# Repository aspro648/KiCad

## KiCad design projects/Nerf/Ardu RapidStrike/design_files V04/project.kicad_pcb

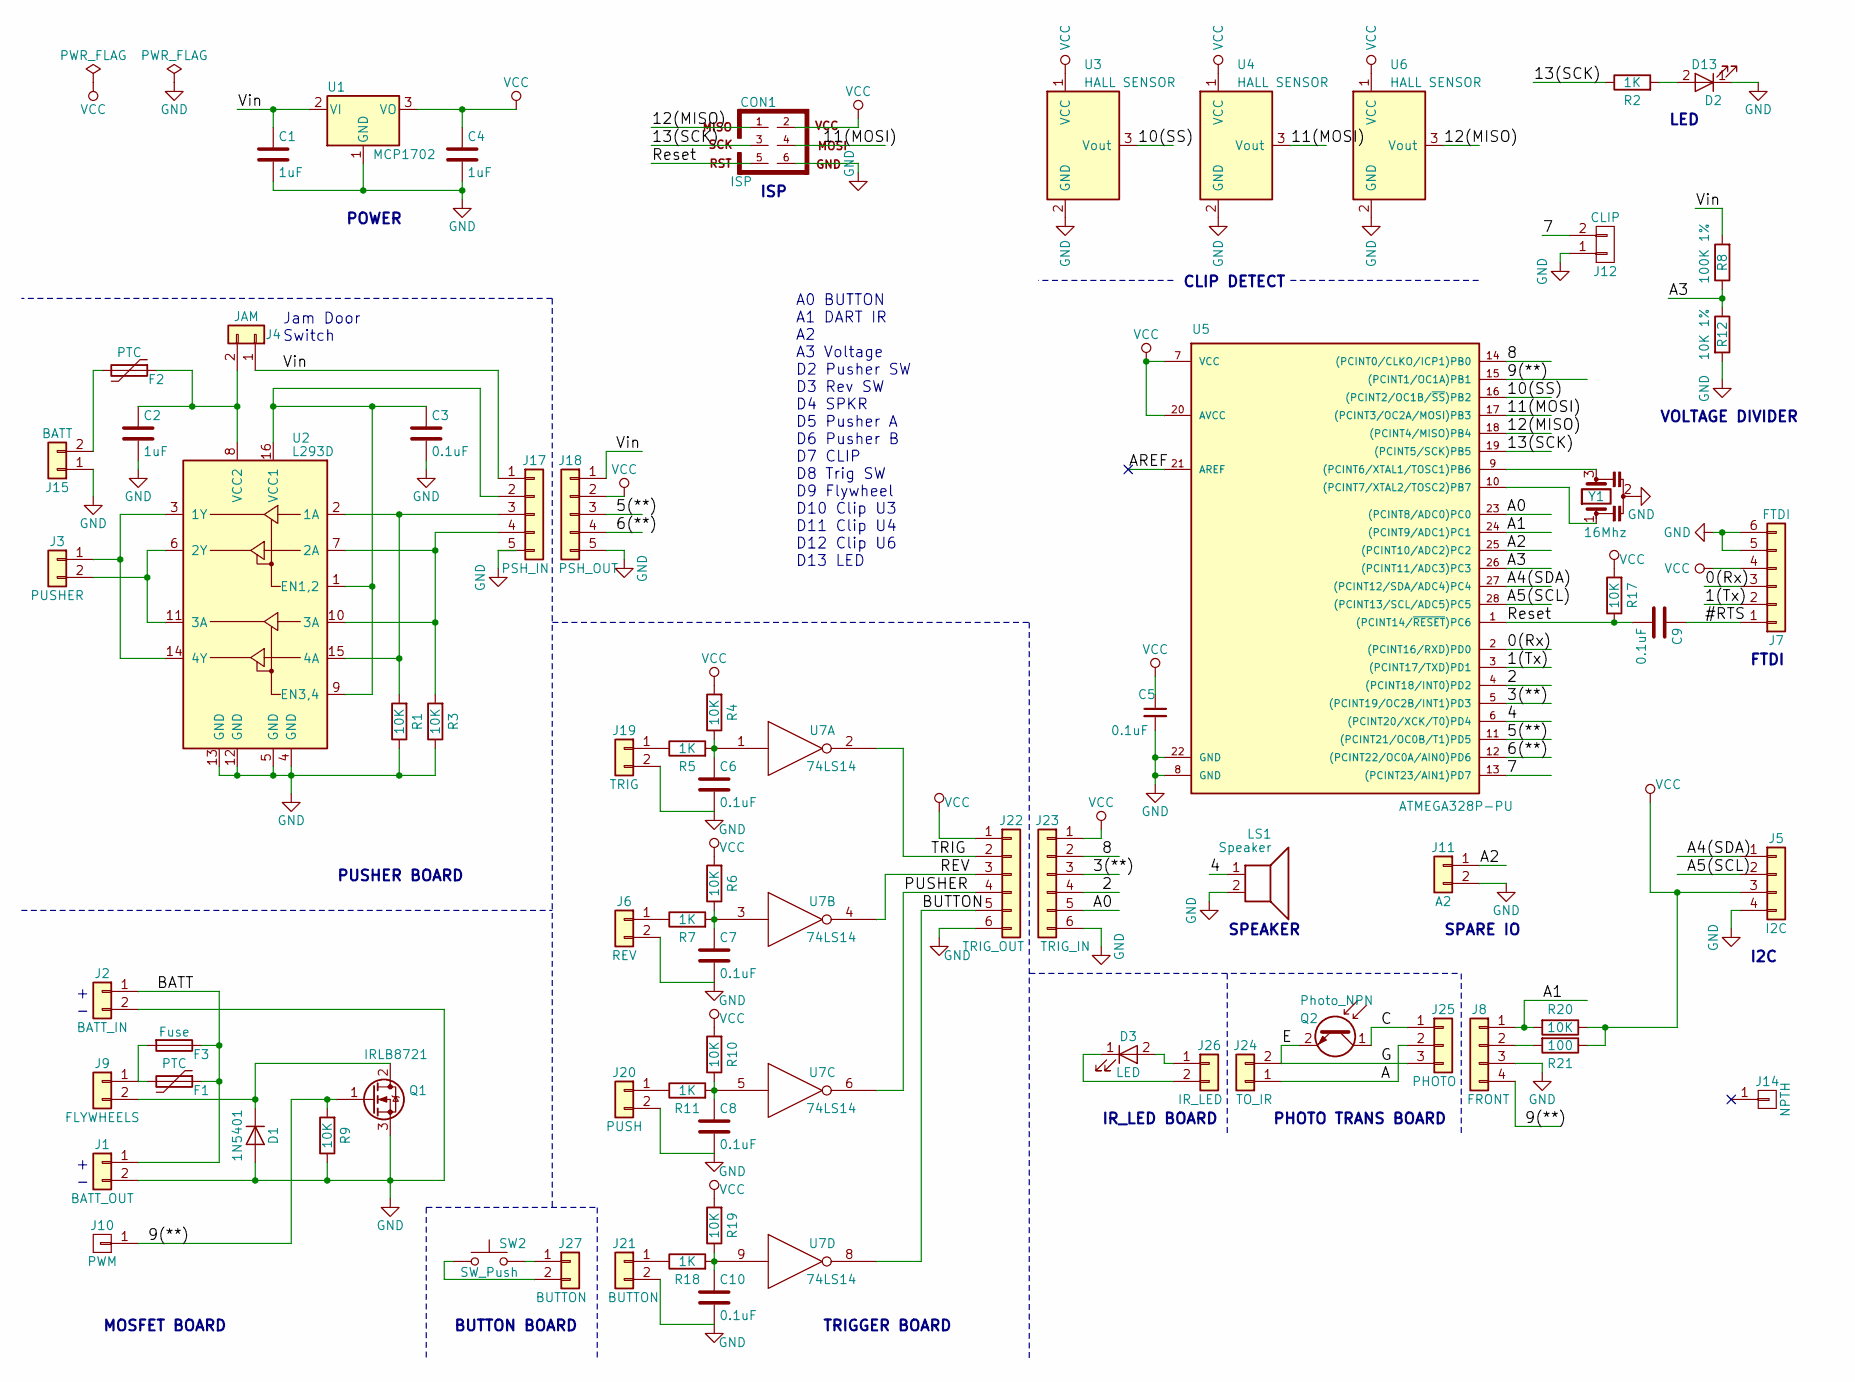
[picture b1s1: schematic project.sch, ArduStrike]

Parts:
C1, C2, C4: 1uF; C_Disc_D5.0mm_W2.5mm_P2.50mm
C3, C5, C6, C7, C8, C9, C10: 0.1uF; C_Disc_D3.4mm_W2.1mm_P2.50mm
CON1: ISP; Pin_Header_Straight_2x03_Pitch2.54mm
D1: 1N5401; D_DO-15_P12.70mm_Horizontal
D2: D13; LED_D3.0mm_Horizontal_O1.27mm_Z10.0mm
D3: LED; LED_D3.0mm
F1, F2: PTC; Fuse_Littelfuse-LVR125
F3: Fuse; BladeFuse-Mini_Keystone_3568
J1: BATT_OUT; TerminalBlock_Phoenix_PT-1,5-2-3.5-H_1x02_P3.50mm_Horizontal
J2: BATT_IN; TerminalBlock_Phoenix_PT-1,5-2-3.5-H_1x02_P3.50mm_Horizontal
J3: PUSHER; TerminalBlock_Phoenix_PT-1,5-2-3.5-H_1x02_P3.50mm_Horizontal
J4: JAM; TerminalBlock_Phoenix_PT-1,5-2-3.5-H_1x02_P3.50mm_Horizontal
J5: I2C; Molex_PicoBlade_53048-0410_04x1.25mm_Angled
J6: REV; Pin_Header_Straight_2x01_Pitch2.00mm
J7: FTDI; Pin_Header_Angled_1x06_Pitch2.54mm
J8: FRONT; Molex_PicoBlade_53048-0410_04x1.25mm_Angled
J9: FLYWHEELS; Flywheel_dual_terminals
J10: PWM; Pin_Header_Straight_1x01_Pitch2.00mm
J11: A2; Pin_Header_Straight_1x02_Pitch2.00mm
J12: CLIP; Molex_PicoBlade_53048-0210_02x1.25mm_Angled
J14: NPTH; SolderWirePad_single_2-5mmDrill
J15: BATT; TerminalBlock_Phoenix_PT-1,5-2-3.5-H_1x02_P3.50mm_Horizontal
J17: PSH_IN; Molex_PicoBlade_53047-0510_05x1.25mm_Straight
J18: PSH_OUT; Molex_PicoBlade_53048-0510_05x1.25mm_Angled
J19: TRIG; Pin_Header_Straight_2x01_Pitch2.00mm
J20: PUSH; Pin_Header_Straight_2x01_Pitch2.00mm
J21: BUTTON; Molex_PicoBlade_53047-0210_02x1.25mm_Straight
J22: TRIG_OUT; Molex_PicoBlade_53048-0610_06x1.25mm_Angled
J23: TRIG_IN; Molex_PicoBlade_53048-0610_06x1.25mm_Angled
J24: TO_IR; Pin_Header_Straight_1x02_Pitch2.00mm
J25: PHOTO; Pin_Header_Straight_1x03_Pitch2.00mm
J26: IR_LED; Pin_Header_Straight_1x02_Pitch2.00mm
J27: BUTTON; Pin_Header_Straight_1x02_Pitch2.00mm
LS1: Speaker; SPEAKER
Q1: IRLB8721; TO-220-3_Horizontal
Q2: Photo_NPN; LED_D3.0mm
R1, R3, R4, R6, R10, R17, R19, R20: 10K; R__P5.08mm
R2: 1K; R_Axial_DIN0204_L3.6mm_D1.6mm_P7.62mm_Horizontal
R5, R7, R11, R18: 1K; R__P5.08mm
R8: 100K 1%; R_Axial_DIN0204_L3.6mm_D1.6mm_P7.62mm_Horizontal
R9: 10K; R_Axial_DIN0204_L3.6mm_D1.6mm_P7.62mm_Horizontal
R12: 10K 1%; R_Axial_DIN0204_L3.6mm_D1.6mm_P7.62mm_Horizontal
R21: 100; R__P5.08mm
SW2: SW_Push; SW_PUSH_6mm
U1: MCP1702; TO-92_Inline_Narrow_Oval
U2: L293D; DIP-16_W7.62mm
U3, U4, U6: HALL SENSOR; Hall_Sensor
U5: ATMEGA328P-PU; DIP-28_W7.62mm
U7: 74LS14; DIP-14_W7.62mm
Y1: 16Mhz; Resonator-3pin_w7.0mm_h2.5mm

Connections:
/0(Rx): J7.3, U5.2 ((PCINT16/RXD)PD0)
/1(Tx): J7.2, U5.3 ((PCINT17/TXD)PD1)
/2: J23.4, U5.4 ((PCINT18/INT0)PD2)
/3(**): J23.3, U5.5 ((PCINT19/OC2B/INT1)PD3)
/4: LS1.1, U5.6 ((PCINT20/XCK/T0)PD4)
/5(**): J18.3, U5.11 ((PCINT21/OC0B/T1)PD5)
/6(**): J18.4, U5.12 ((PCINT22/OC0A/AIN0)PD6)
/7: J12.2, U5.13 ((PCINT23/AIN1)PD7)
/8: J23.2, U5.14 ((PCINT0/CLKO/ICP1)PB0)
/9(**): J8.4, J10.1, Q1.1 (G), R9.2, U5.15 ((PCINT1/OC1A)PB1)
/10(SS): U3.3 (Vout), U5.16 ((PCINT2/OC1B/~SS~)PB2)
/11(MOSI): CON1.4, U4.3 (Vout), U5.17 ((PCINT3/OC2A/MOSI)PB3)
/12(MISO): CON1.1, U5.18 ((PCINT4/MISO)PB4), U6.3 (Vout)
/13(SCK): CON1.3, R2.1, U5.19 ((PCINT5/SCK)PB5)
/#RTS: C9.1, J7.1
/A: J24.1, J25.2
/A0: J23.5, U5.23 ((PCINT8/ADC0)PC0)
/A1: J8.1, R20.2, U5.24 ((PCINT9/ADC1)PC1)
/A2: J11.1, U5.25 ((PCINT10/ADC2)PC2)
/A3: R8.1, R12.1, U5.26 ((PCINT11/ADC3)PC3)
/A4(SDA): J5.1, U5.27 ((PCINT12/SDA/ADC4)PC4)
/A5(SCL): J5.2, U5.28 ((PCINT13/SCL/ADC5)PC5)
/AREF: U5.21 (AREF)
/BATT: F1.1, F3.1, J1.1, J2.1
/BUTTON: J22.5, U7.8
/C: J25.1, Q2.1 (C)
/E: J24.2, J25.3, Q2.2 (E)
/PUSHER: J22.4, U7.6
/REV: J22.3, U7.4
/Reset: C9.2, CON1.5, R17.1, U5.1 ((PCINT14/~RESET~)PC6)
/TRIG: J22.2, U7.2
/Vin: C1.1, J4.1, J17.1, J18.1, R8.2, U1.2 (VI)
GND: C1.2, C2.2, C3.2, C4.2, C5.2, C6.2, C7.2, C8.2, C10.2, CON1.6, D1.2 (A), D2.1 (K), J1.2, J2.2, J5.4, J6.2, J7.5, J7.6, J8.3, J11.2, J12.1, J15.1, J17.5, J18.5, J19.2, J20.2, J21.2, J22.6, J23.6, LS1.2, Q1.3 (S), R1.1, R3.1, R9.1, R12.2, U1.1 (GND), U2.4 (GND), U2.5 (GND), U2.12 (GND), U2.13 (GND), U3.2 (GND), U4.2 (GND), U5.8 (GND), U5.22 (GND), U6.2 (GND), U7.7 (GND), Y1.2
unnamed: C2.1, F2.1, J4.2, U2.8 (VCC2)
unnamed: C3.1, J17.2, U2.1 (EN1,2), U2.9 (EN3,4), U2.16 (VCC1)
unnamed: C6.1, R4.1, R5.2, U7.1
unnamed: C7.1, R6.1, R7.2, U7.3
unnamed: C8.1, R10.1, R11.2, U7.5
unnamed: C10.1, R18.2, R19.1, U7.9
unnamed: D1.1 (K), J9.2, Q1.2 (D)
unnamed: D2.2 (A), R2.2
unnamed: D3.1 (K), J26.2
unnamed: D3.2 (A), J26.1
unnamed: F1.2, F3.2, J9.1
unnamed: F2.2, J15.2
unnamed: J3.1, U2.3 (1Y), U2.14 (4Y)
unnamed: J3.2, U2.6 (2Y), U2.11 (3A)
unnamed: J6.1, R7.1
unnamed: J8.2, R21.2
unnamed: J17.3, R1.2, U2.2 (1A), U2.15 (4A)
unnamed: J17.4, R3.2, U2.7 (2A), U2.10 (3A)
unnamed: J19.1, R5.1
unnamed: J20.1, R11.1
unnamed: J21.1, R18.1
unnamed: J27.1, SW2.2
unnamed: J27.2, SW2.1
unnamed: U5.9 ((PCINT6/XTAL1/TOSC1)PB6), Y1.3
unnamed: U5.10 ((PCINT7/XTAL2/TOSC2)PB7), Y1.1
VCC: C4.1, C5.1, CON1.2, J5.3, J7.4, J18.2, J22.1, J23.1, R4.2, R6.2, R10.2, R17.2, R19.2, R20.1, R21.1, U1.3 (VO), U3.1 (VCC), U4.1 (VCC), U5.7 (VCC), U5.20 (AVCC), U6.1 (VCC), U7.14 (VCC)

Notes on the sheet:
Jam Door Switch
VOLTAGE DIVIDER
CLIP DETECT
+ -
TRIGGER BOARD
MOSFET BOARD
PUSHER BOARD
BUTTON BOARD
PHOTO TRANS BOARD
IR_LED BOARD
A0 BUTTON A1 DART IR A2 A3 Voltage D2 Pusher SW D3 Rev SW D4 SPKR D5 Pusher A D6 Pusher B D7 CLIP D8 Trig SW D9 Flywheel D10 Clip U3 D11 Clip U4 D12 Clip U6 D13 LED
SPARE IO
FTDI
I2C
ISP
POWER
SPEAKER
LED

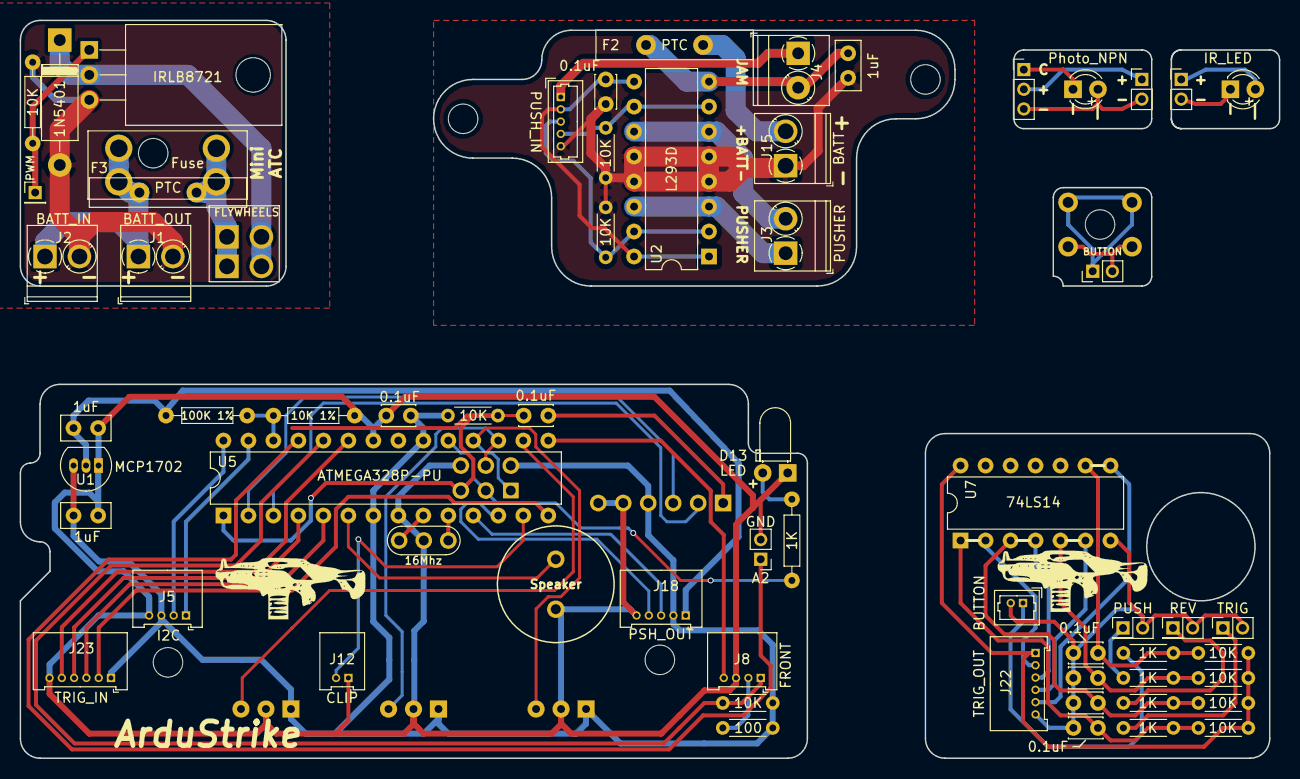
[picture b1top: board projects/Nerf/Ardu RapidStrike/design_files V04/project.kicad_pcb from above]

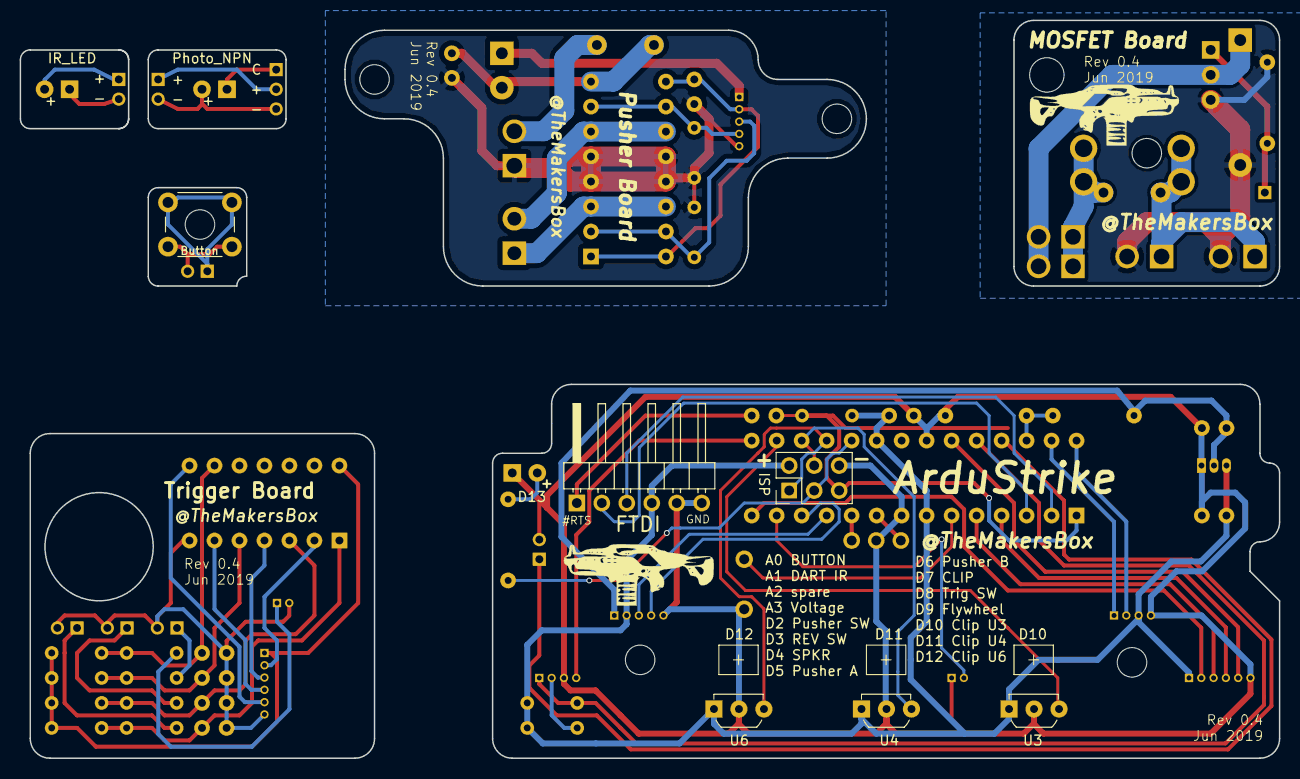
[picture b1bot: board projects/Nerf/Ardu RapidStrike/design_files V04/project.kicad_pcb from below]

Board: 2 copper layers, 128.0 x 75.0 mm, 76 parts (6 on the bottom side), 58 nets.

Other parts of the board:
J13: BUTTON; SolderWirePad_single_2-5mmDrill
J14#2, J14#3, J14#4, J14#5: NPTH; SolderWirePad_single_2-5mmDrill

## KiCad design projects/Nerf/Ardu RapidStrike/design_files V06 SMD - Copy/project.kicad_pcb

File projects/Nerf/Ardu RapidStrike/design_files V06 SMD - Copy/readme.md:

ArduStrike

MOSFET Board
-------------
- 1 ea., MOSFET N-CH 30V 62A TO-220AB, Infineon IRLB8721PBF, https://www.digikey.com/short/p4fhcm
- 1 ea., 1A Diode, S1KB
- 1 ea., 10K Resistors, 1/8W 5% generic, https://www.digikey.com/short/p4frj2 
- 1 ea., PTC RESET FUSE 16V 2.5A 2920SMD, https://www.digikey.com/short/p5cb11
- 3 ea., 2 POS 5.08mm terminal, https://www.digikey.com/short/p9tv29
- 1 ea., PTC Fuse 2.5A 1812, https://www.digikey.com/short/p5cbvf

Pusher Fuse 1206: 1A https://www.digikey.com/short/p532qq
Main: 1812: 3.5A https://www.digikey.com/short/p532pr

Pusher Board
-------------
- 1 ea., L293 H-Bridge, STMicroelectronics L293NE, https://www.digikey.com/short/pm20fd
- 2 ea., 10K Resistors, 1/8W 5% generic, https://www.digikey.com/short/p4frj2 
- 1 ea., CER 0.1UF 25V Y5V RADIAL 2.5mm lead spacing, generic, https://www.digikey.com/short/jn9pm2
- 1 ea., CER 1UF 25V X7R RADIAL 2.5 lead spacing, generic https://www.digikey.com/short/p4fr3w
- 1 ea., 5POS Picoblade header VERT, Molex 0530470510, https://www.digikey.com/short/pm2n8f
- 1 ea., PTC RESET FUSE 16V 2.5A RADIAL, https://www.digikey.com/short/pm20nc
- 2 ea., 2 POS 3.5mm terminal, https://www.digikey.com/short/p9tvn0
- 1 ea., 2 POS 5.08mm header, https://www.digikey.com/short/p9tv29

Trigger Board
--------------
- 1 ea., IC INVERTER SCHMITT 6CH 14DIP, TI SN74HC14N, https://www.digikey.com/short/pmzjfv
- 4 ea., CER 0.1UF 25V Y5V RADIAL 2.5mm lead spacing, generic, https://www.digikey.com/short/jn9pm2
- 4 ea., 1K Ohm Resistors, 1/8W 5% generic, https://www.digikey.com/short/p4fr81
- 4 ea., 10K Resistors, 1/8W 5% generic, https://www.digikey.com/short/p4frj2 
- 1 ea., 6POS PicoBlade header, https://www.digikey.com/short/p4wz22
- 1 ea., 2POS Picoblade header, https://www.digikey.com/short/p4wz0w

Main Board
----------------
- 1 ea., IC MCU 8BIT 32KB FLASH 32TQFP, https://www.digikey.com/short/p5cb88
- 1 ea., Y1 CER RES 16.0000MHZ 15PF SMD, CSTCE16M0V53-R0, https://www.digikey.com/short/j2b9cm
- 1 ea., IC REG LINEAR 5V 250MA SOT89-3, Microchip MCP1702-5002E/TO, https://www.digikey.com/short/p5cbrh
- 3 ea., Hall Effect Sensor, Diodes Incorporated AH9246-P-B, https://www.digikey.com/short/p5cb4f
- 1 ea., 0.96 Inch 128x64 I2C OLED, https://www.amazon.com/gp/product/B072Q2X2LL/
- 1 ea., Header 6 POS RA, 

- 2 ea., CER 0.1UF 25V Y5V RADIAL 2.5mm lead spacing, generic, https://www.digikey.com/short/jn9pm2
- 2 ea., CER 1UF 25V X7R RADIAL 2.5 lead spacing, generic https://www.digikey.com/short/p4fr3w

- 1 ea., 3mm LED red, https://www.digikey.com/short/pmwzdf
- 1 ea., 3mm IR LED, https://www.digikey.com/short/pmwzdq
- 1 ea., NPN photo transistor, https://www.digikey.com/short/pmwzdb

- 1 ea., 100 ohm resistor 1/8W 5% generic, https://www.digikey.com/short/pmwz22
- 1 ea., 1K ohm resistor 1/8W 5% generic, https://www.digikey.com/short/pmwzwq
- 2 ea., 10K Resistors, 1/8W 5% generic, https://www.digikey.com/short/p4frj2 

- 1 ea., 10K Resistors, 1/4W 1%, https://www.digikey.com/short/p4fr2q
- 1 ea., 100K Resistors, 1/4W 1%, https://www.digikey.com/short/p9tnc3

- 1 ea., SWITCH TACTILE SPST-NO 0.05A 24V, https://www.digikey.com/short/p4w42v
- 1 ea., Piezo speaker, TDK PS1240P02CT3,  https://www.digikey.com/short/pmwzfc

- 1 ea., 2POS Picoblade header, https://www.digikey.com/short/p4wz0w
- 1 ea., 2POS PicoBlade housing, https://www.digikey.com/short/p4wz0d

- 1 ea., 3POS Picoblade header, https://www.digikey.com/short/pmwzfb
- 1 ea., 3POS PicoBlade housing, https://www.digikey.com/short/pmwzf2

- 1 ea., 4POS Picoblade header, https://www.digikey.com/short/p4wz0m
- 2 ea., 4POS PicoBlade housing, https://www.digikey.com/short/p4wzd1

- 1 ea., 5POS Picoblade header, https://www.digikey.com/short/p4wzdp
- 2 ea., 5POS PicoBlade housing, https://www.digikey.com/short/p4wzdb

- 1 ea., 6POS PicoBlade header, https://www.digikey.com/short/p4wz22
- 2 ea., 6POS PicoBlade housing, https://www.digikey.com/short/p4wz28

12" PRE-CRIMP 1853 RED, https://www.digikey.com/short/p4wzvf
12" PRE-CRIMP 1853 BLACK, https://www.digikey.com/short/p4wz1p
12" PRE-CRIMP 1853 BLUE, https://www.digikey.com/short/p4wz14
12" PRE-CRIMP 1853 ORANGE, https://www.digikey.com/short/p4wz1r
12" PRE-CRIMP 1853 GREEN, https://www.digikey.com/short/p4w4c4

10" PRE-CRIMP 1852 RED, https://www.digikey.com/short/p937zh
10" PRE-CRIMP 1852 BLACK, https://www.digikey.com/short/p937zv
10" PRE-CRIMP 1852 YELLOW, https://www.digikey.com/short/p9374t
10" PRE-CRIMP 1852 GREEN, https://www.digikey.com/short/p9374z
10" PRE-CRIMP 1852 ORANGE, https://www.digikey.com/short/p9374f
10" PRE-CRIMP 1852 BLUE, https://www.digikey.com/short/p937mc

16 AWG Silicone wire, https://www.amazon.com/BNTECHGO-Silicone-Flexible-Strands-Stranded/dp/B00TG1TRL2
18 AWG Silicone wire (7.5A, $0.40/ft), https://www.amazon.com/Silicone-Electrical-Conductor-Parallel-Flexible/dp/B07FMRDP87
16 AWG Silicone wire (12A, $0.70/ft), https://www.amazon.com/Silicone-Electrical-Conductor-Parallel-Flexible/dp/B07FMLVF84

XT60 connector male

Optional:
FTDI SERIAL TTL-232 USB CABLE, https://www.digikey.com/short/p4w47d
SPARKFUN FT231X BREAKOUT, https://www.digikey.com/short/p4w4qb

Motor Spec Sheet:
----------------
https://docs.google.com/spreadsheets/d/12gOU-GbuqdGVzpOjZJvQ_gq1Nmw63c_sd13Wt4bfn1E/edit#gid=0

Revisions
----------------
0.1 Added push button to A0.
0.3 Removed XT30 connectors, added PTC, fuse holder.
0.4 Major component repositioning
0.5 Trigger moved clip connector
	Pusher Bat conn to 5.08mm.
	Mosfet layout change

License
----------------
[Attribution-ShareAlike 3.0 United States (CC BY-SA 3.0 US)](https://creativecommons.org/licenses/by-sa/3.0/us/)

You are free to:

- Share — copy and redistribute the material in any medium or format
- Adapt — remix, transform, and build upon the material

Under the following terms:

- Attribution — You must give appropriate credit, provide a link to the license, and indicate if changes were made. You may do so in any reasonable manner, but not in any way that suggests the licensor endorses you or your use.
- ShareAlike — If you remix, transform, or build upon the material, you must distribute your contributions under the same license as the original.

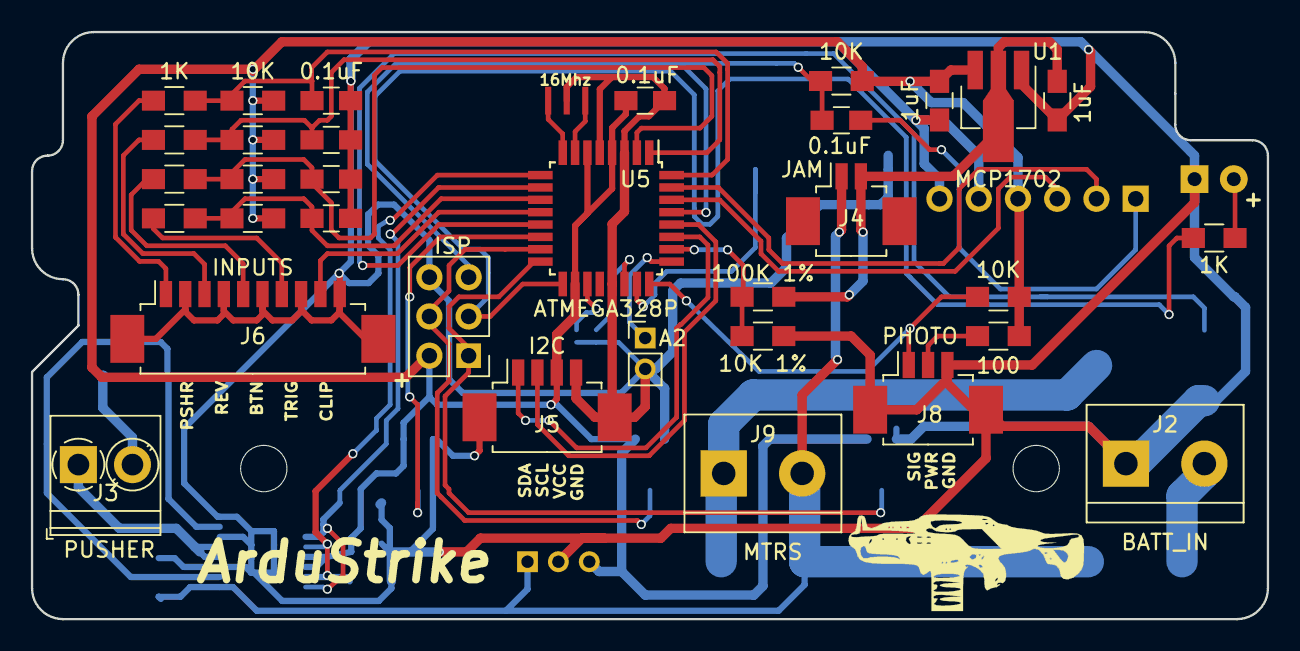
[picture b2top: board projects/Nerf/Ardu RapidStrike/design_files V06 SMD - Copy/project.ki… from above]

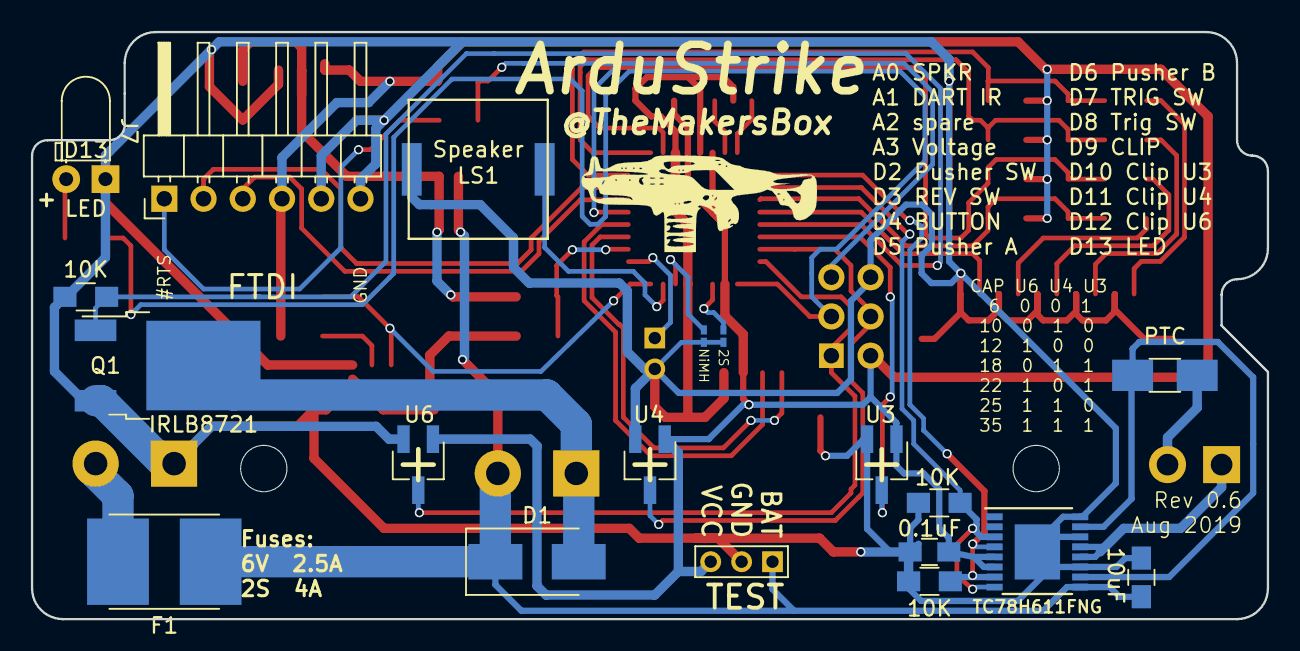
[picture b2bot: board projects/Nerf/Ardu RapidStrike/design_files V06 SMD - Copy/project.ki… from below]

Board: 2 copper layers, 80.0 x 38.0 mm, 55 parts (19 on the bottom side), 41 nets.

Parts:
C1, C4: 1uF; C_0805_HandSoldering
C2: 10uF; C_0805_HandSoldering
C3, C5, C6, C7, C8, C9, C10: 0.1uF; C_0805_HandSoldering
CON1: ISP; Pin_Header_Straight_2x03_Pitch2.54mm
D1: KICKBACK; D_SMB_Handsoldering
D13: LED; LED_D3.0mm_Horizontal_O1.27mm_Z10.0mm
F1: PTC; Fuse_SMD2920
F2: PTC; Fuse_SMD1206_HandSoldering
J1: TEST; Pin_Header_Straight_1x03_Pitch2.00mm
J2: BATT_IN; TerminalBlock_bornier-2_P5.08mm
J3: PUSHER; TerminalBlock_Phoenix_PT-1,5-2-3.5-H_1x02_P3.50mm_Horizontal
J4: JAM; Molex_PicoBlade_53261-0271_02x1.25mm_Angled
J5: I2C; Molex_PicoBlade_53261-0471_04x1.25mm_Angled
J6: INPUTS; Molex_PicoBlade_53261-1071_10x1.25mm_Angled
J7: FTDI; Pin_Header_Angled_1x06_Pitch2.54mm
J8: PHOTO; Molex_PicoBlade_53261-0371_03x1.25mm_Angled
J9: MTRS; TerminalBlock_bornier-2_P5.08mm
J11: A2; Pin_Header_Straight_1x02_Pitch2.00mm
J14, J14#2: NPTH; SolderWirePad_single_2-5mmDrill
JP1: 2S; JMPR
JP2: NiMH; JMPR
LS1: Speaker; PS1240_piezo
Q1: IRLB8721; TO-252-2_hand_soldering
R1, R3, R4, R6, R9, R10, R17, R19, R20: 10K; R_0805_HandSoldering
R2, R5, R7, R11, R18: 1K; R_0805_HandSoldering
R8: 100K 1%; R_0805_HandSoldering
R12: 10K 1%; R_0805_HandSoldering
R21: 100; R_0805_HandSoldering
U1: MCP1702; SOT-89-3_Handsoldering
U2: TC78H611FNG; TSSOP-16-1EP_4.4x5mm_Pitch0.65mm
U3, U4, U6: HALL SENSOR; SC-59_Handsoldering
U5: ATMEGA328P; TQFP-32_7x7mm_Pitch0.8mm
Y1: 16Mhz; Resonator_SMD_CTSC_1.3mmx3.2mm

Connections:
/0(Rx): J7.3, U5.30
/1(Tx): J7.2, U5.31
/2: C6.1, R4.1, R5.2, U5.32
/3(**): C7.1, R6.1, R7.2, U5.1
/4: C10.1, R18.2, R19.1, U5.2
/5(**): R1.2, U2.4, U2.7, U5.9
/6(**): R3.2, U2.3, U2.8, U5.10
/7: C8.1, R10.1, R11.2, U5.11
/8: J6.9, U5.12
/9(**): Q1.1, R9.2, U5.13
/10(SS): U3.3, U5.14
/11(MOSI): CON1.4, U4.3, U5.15
/12(MISO): CON1.1, U5.16, U6.3
/13(SCK): CON1.3, R2.1, U5.17
/#RTS: C9.1, J7.1
/A0: LS1.1, U5.23
/A1: J8.1, R20.2, U5.24
/A2: J11.1, U5.25
/A3: R8.1, R12.1, U5.26
/A4(SDA): J5.1, U5.27
/A5(SCL): J5.2, U5.28
/BATT: C2.1, D1.1, F1.1, J1.1, J4.1, J9.2, U2.9
/Reset: C9.2, CON1.5, R17.1, U5.29
/Vin: C1.1, J4.2, R8.2, U1.2
GND: C1.2, C2.2, C3.2, C4.2, C5.2, C6.2, C7.2, C8.2, C10.2, CON1.6, D13.1, J1.2, J2.1, J5.4, J6.2, J6.4, J6.6, J6.8, J6.10, J7.5, J7.6, J8.3, J11.2, JP1.1, JP2.1, LS1.2, Q1.3, R1.1, R3.1, R9.1, R12.2, U1.1, U2.11, U2.14, U2.16, U3.2, U4.2, U5.3, U5.5, U5.21, U6.2, Y1.2
unnamed: D1.2, J9.1, Q1.2
unnamed: D13.2, R2.2
unnamed: F1.2, J2.2
unnamed: F2.1, U2.10, U2.15
unnamed: F2.2, J3.2
unnamed: J3.1, U2.12, U2.13
unnamed: J6.1, R5.1
unnamed: J6.3, R7.1
unnamed: J6.5, R18.1
unnamed: J6.7, R11.1
unnamed: J8.2, R21.2
unnamed: JP1.2, U5.19
unnamed: JP2.2, U5.22
unnamed: U5.7, Y1.3
unnamed: U5.8, Y1.1
VCC: C3.1, C4.1, C5.1, CON1.2, J1.3, J5.3, J7.4, R4.2, R6.2, R10.2, R17.2, R19.2, R20.1, R21.1, U1.3, U2.5, U2.6, U3.1, U4.1, U5.4, U5.6, U5.18, U6.1

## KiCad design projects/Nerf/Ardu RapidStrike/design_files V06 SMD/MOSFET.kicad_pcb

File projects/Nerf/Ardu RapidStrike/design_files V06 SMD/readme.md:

ArduStrike

MOSFET Board
-------------
- 1 ea., MOSFET N-CH 30V 62A TO-220AB, Infineon IRLB8721PBF, https://www.digikey.com/short/p4fhcm
- 1 ea., 1A Diode, S1KB
- 1 ea., 10K Resistors, 1/8W 5% generic, https://www.digikey.com/short/p4frj2 
- 1 ea., PTC RESET FUSE 16V 2.5A 2920SMD, https://www.digikey.com/short/p5cb11
- 3 ea., 2 POS 5.08mm terminal, https://www.digikey.com/short/p9tv29
- 1 ea., PTC Fuse 2.5A 1812, https://www.digikey.com/short/p5cbvf

Pusher Board
-------------
- 1 ea., L293 H-Bridge, STMicroelectronics L293NE, https://www.digikey.com/short/pm20fd
- 2 ea., 10K Resistors, 1/8W 5% generic, https://www.digikey.com/short/p4frj2 
- 1 ea., CER 0.1UF 25V Y5V RADIAL 2.5mm lead spacing, generic, https://www.digikey.com/short/jn9pm2
- 1 ea., CER 1UF 25V X7R RADIAL 2.5 lead spacing, generic https://www.digikey.com/short/p4fr3w
- 1 ea., 5POS Picoblade header VERT, Molex 0530470510, https://www.digikey.com/short/pm2n8f
- 1 ea., PTC RESET FUSE 16V 2.5A RADIAL, https://www.digikey.com/short/pm20nc
- 2 ea., 2 POS 3.5mm terminal, https://www.digikey.com/short/p9tvn0
- 1 ea., 2 POS 5.08mm header, https://www.digikey.com/short/p9tv29

Trigger Board
--------------
- 1 ea., IC INVERTER SCHMITT 6CH 14DIP, TI SN74HC14N, https://www.digikey.com/short/pmzjfv
- 4 ea., CER 0.1UF 25V Y5V RADIAL 2.5mm lead spacing, generic, https://www.digikey.com/short/jn9pm2
- 4 ea., 1K Ohm Resistors, 1/8W 5% generic, https://www.digikey.com/short/p4fr81
- 4 ea., 10K Resistors, 1/8W 5% generic, https://www.digikey.com/short/p4frj2 
- 1 ea., 6POS PicoBlade header, https://www.digikey.com/short/p4wz22
- 1 ea., 2POS Picoblade header, https://www.digikey.com/short/p4wz0w

Main Board
----------------
- 1 ea., IC MCU 8BIT 32KB FLASH 32TQFP, https://www.digikey.com/short/p5cb88
- 1 ea., Y1 CER RES 16.0000MHZ 15PF SMD, CSTCE16M0V53-R0, https://www.digikey.com/short/j2b9cm
- 1 ea., IC REG LINEAR 5V 250MA SOT89-3, Microchip MCP1702-5002E/TO, https://www.digikey.com/short/p5cbrh
- 3 ea., Hall Effect Sensor, Diodes Incorporated AH9246-P-B, https://www.digikey.com/short/p5cb4f
- 1 ea., 0.96 Inch 128x64 I2C OLED, https://www.amazon.com/gp/product/B072Q2X2LL/
- 1 ea., Header 6 POS RA, 

- 2 ea., CER 0.1UF 25V Y5V RADIAL 2.5mm lead spacing, generic, https://www.digikey.com/short/jn9pm2
- 2 ea., CER 1UF 25V X7R RADIAL 2.5 lead spacing, generic https://www.digikey.com/short/p4fr3w

- 1 ea., 3mm LED red, https://www.digikey.com/short/pmwzdf
- 1 ea., 3mm IR LED, https://www.digikey.com/short/pmwzdq
- 1 ea., NPN photo transistor, https://www.digikey.com/short/pmwzdb

- 1 ea., 100 ohm resistor 1/8W 5% generic, https://www.digikey.com/short/pmwz22
- 1 ea., 1K ohm resistor 1/8W 5% generic, https://www.digikey.com/short/pmwzwq
- 2 ea., 10K Resistors, 1/8W 5% generic, https://www.digikey.com/short/p4frj2 

- 1 ea., 10K Resistors, 1/4W 1%, https://www.digikey.com/short/p4fr2q
- 1 ea., 100K Resistors, 1/4W 1%, https://www.digikey.com/short/p9tnc3

- 1 ea., SWITCH TACTILE SPST-NO 0.05A 24V, https://www.digikey.com/short/p4w42v
- 1 ea., Piezo speaker, TDK PS1240P02CT3,  https://www.digikey.com/short/pmwzfc

- 1 ea., 2POS Picoblade header, https://www.digikey.com/short/p4wz0w
- 1 ea., 2POS PicoBlade housing, https://www.digikey.com/short/p4wz0d

- 1 ea., 3POS Picoblade header, https://www.digikey.com/short/pmwzfb
- 1 ea., 3POS PicoBlade housing, https://www.digikey.com/short/pmwzf2

- 1 ea., 4POS Picoblade header, https://www.digikey.com/short/p4wz0m
- 2 ea., 4POS PicoBlade housing, https://www.digikey.com/short/p4wzd1

- 1 ea., 5POS Picoblade header, https://www.digikey.com/short/p4wzdp
- 2 ea., 5POS PicoBlade housing, https://www.digikey.com/short/p4wzdb

- 1 ea., 6POS PicoBlade header, https://www.digikey.com/short/p4wz22
- 2 ea., 6POS PicoBlade housing, https://www.digikey.com/short/p4wz28

12" PRE-CRIMP 1853 RED, https://www.digikey.com/short/p4wzvf
12" PRE-CRIMP 1853 BLACK, https://www.digikey.com/short/p4wz1p
12" PRE-CRIMP 1853 BLUE, https://www.digikey.com/short/p4wz14
12" PRE-CRIMP 1853 ORANGE, https://www.digikey.com/short/p4wz1r
12" PRE-CRIMP 1853 GREEN, https://www.digikey.com/short/p4w4c4

10" PRE-CRIMP 1852 RED, https://www.digikey.com/short/p937zh
10" PRE-CRIMP 1852 BLACK, https://www.digikey.com/short/p937zv
10" PRE-CRIMP 1852 YELLOW, https://www.digikey.com/short/p9374t
10" PRE-CRIMP 1852 GREEN, https://www.digikey.com/short/p9374z
10" PRE-CRIMP 1852 ORANGE, https://www.digikey.com/short/p9374f
10" PRE-CRIMP 1852 BLUE, https://www.digikey.com/short/p937mc

16 AWG Silicone wire, https://www.amazon.com/BNTECHGO-Silicone-Flexible-Strands-Stranded/dp/B00TG1TRL2
18 AWG Silicone wire (7.5A, $0.40/ft), https://www.amazon.com/Silicone-Electrical-Conductor-Parallel-Flexible/dp/B07FMRDP87
16 AWG Silicone wire (12A, $0.70/ft), https://www.amazon.com/Silicone-Electrical-Conductor-Parallel-Flexible/dp/B07FMLVF84

XT60 connector male

Optional:
FTDI SERIAL TTL-232 USB CABLE, https://www.digikey.com/short/p4w47d
SPARKFUN FT231X BREAKOUT, https://www.digikey.com/short/p4w4qb

Motor Spec Sheet:
----------------
https://docs.google.com/spreadsheets/d/12gOU-GbuqdGVzpOjZJvQ_gq1Nmw63c_sd13Wt4bfn1E/edit#gid=0

Revisions
----------------
0.1 Added push button to A0.
0.3 Removed XT30 connectors, added PTC, fuse holder.
0.4 Major component repositioning
0.5 Trigger moved clip connector
	Pusher Bat conn to 5.08mm.
	Mosfet layout change

License
----------------
[Attribution-ShareAlike 3.0 United States (CC BY-SA 3.0 US)](https://creativecommons.org/licenses/by-sa/3.0/us/)

You are free to:

- Share — copy and redistribute the material in any medium or format
- Adapt — remix, transform, and build upon the material

Under the following terms:

- Attribution — You must give appropriate credit, provide a link to the license, and indicate if changes were made. You may do so in any reasonable manner, but not in any way that suggests the licensor endorses you or your use.
- ShareAlike — If you remix, transform, or build upon the material, you must distribute your contributions under the same license as the original.

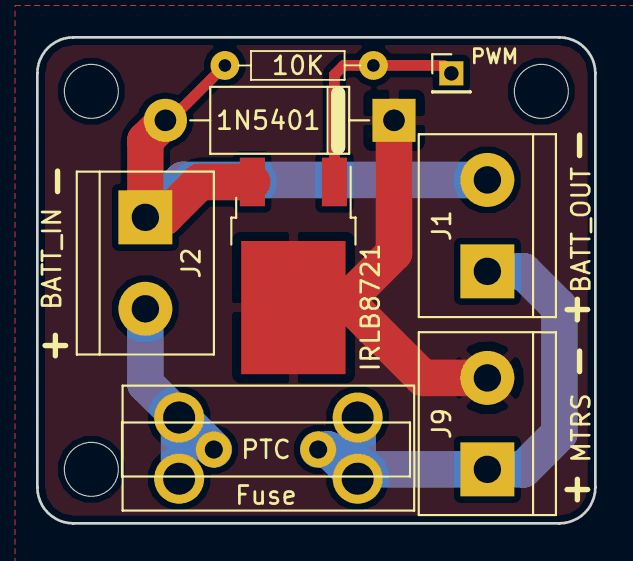
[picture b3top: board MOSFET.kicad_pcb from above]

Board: 2 copper layers, 31.0 x 27.0 mm, 12 parts (0 on the bottom side), 5 nets.

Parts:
D1: 1N5401; D_DO-15_P12.70mm_Horizontal
F1: PTC; Fuse_Littelfuse-LVR125
F3: Fuse; BladeFuse-Mini_Keystone_3568
J1: BATT_OUT; TerminalBlock_bornier-2_P5.08mm
J2: BATT_IN; TerminalBlock_bornier-2_P5.08mm
J9: MTRS; TerminalBlock_bornier-2_P5.08mm
J10: PWM; Pin_Header_Straight_1x01_Pitch2.00mm
J14, J14#2, J14#3: NPTH; SolderWirePad_single_2-5mmDrill
Q1: IRLB8721; TO-252-2_hand_soldering
R9: 10K; R_Axial_DIN0204_L3.6mm_D1.6mm_P7.62mm_Horizontal

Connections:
/9(**): J10.1, Q1.1, R9.2
/BATT: F1.1, F3.1, J2.2
GND: D1.2, J1.2, J2.1, Q1.3, R9.1
unnamed: D1.1, J9.2, Q1.2
unnamed: F1.2, F3.2, J1.1, J9.1
